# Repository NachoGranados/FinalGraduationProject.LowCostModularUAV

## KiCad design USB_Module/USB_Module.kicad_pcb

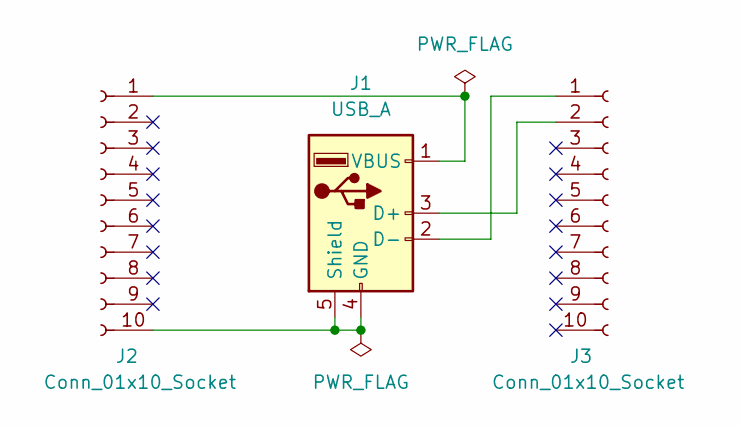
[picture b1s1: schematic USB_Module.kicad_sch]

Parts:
J1: USB_A; USB_A_TE_292303-7_Horizontal
J2, J3: Conn_01x10_Socket; PinSocket_1x10_P2.00mm_Vertical

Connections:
unnamed: J1.3 (D+), J3.2
unnamed: J1.2 (D-), J3.1
unnamed: J1.4 (GND), J1.5 (Shield), J2.10
unnamed: J1.1 (VBUS), J2.1

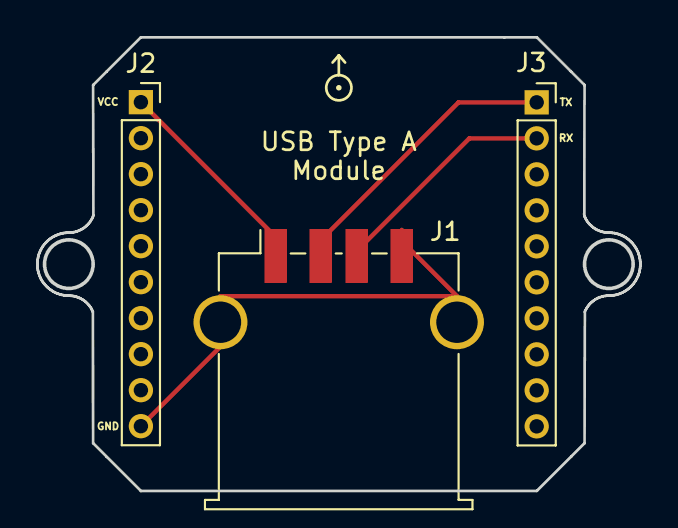
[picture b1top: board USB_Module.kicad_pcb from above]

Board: 2 copper layers, 33.5 x 25.2 mm, 4 parts (0 on the bottom side), 4 nets.

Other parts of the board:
EXP_ORIENTATION: VAL**; EXP_ORIENTATION
